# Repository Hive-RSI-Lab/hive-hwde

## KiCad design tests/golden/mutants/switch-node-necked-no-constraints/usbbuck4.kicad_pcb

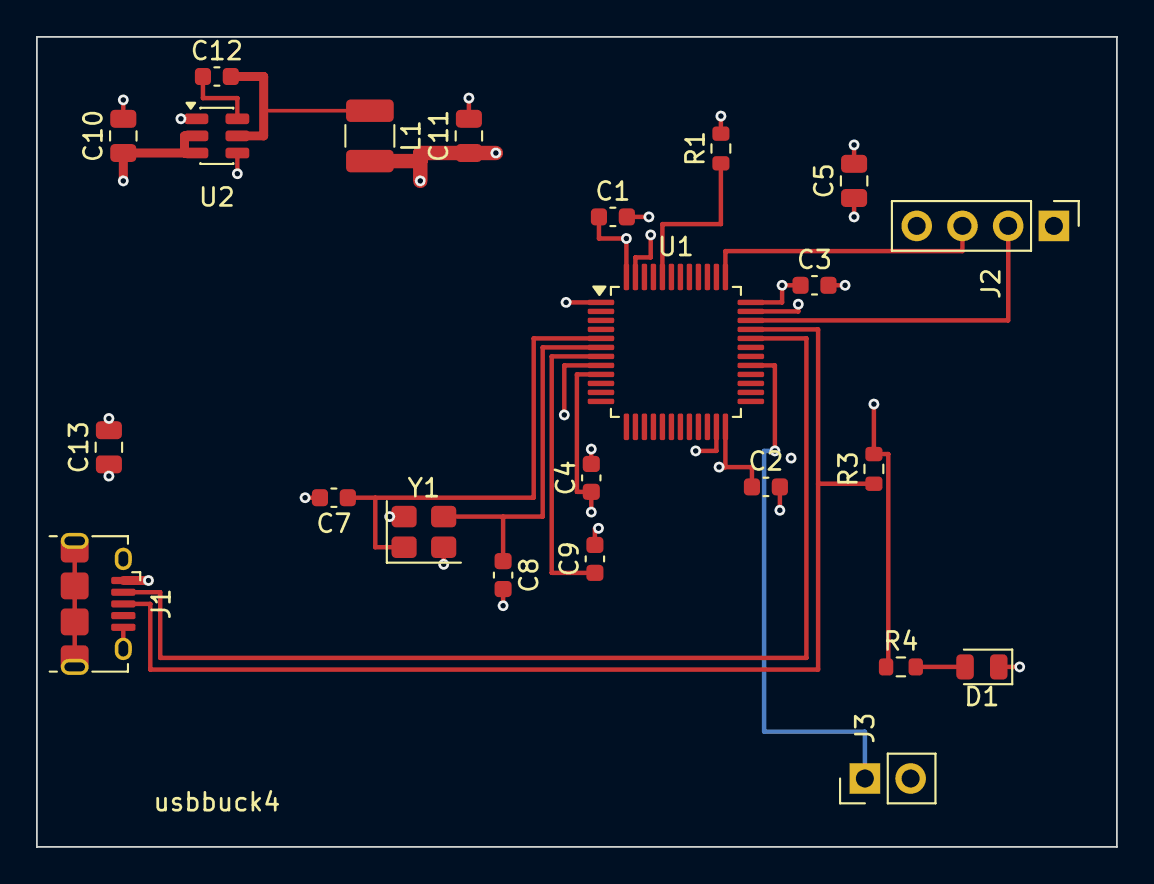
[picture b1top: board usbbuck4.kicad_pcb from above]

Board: 4 copper layers, 60.0 x 45.0 mm, 23 parts (0 on the bottom side), 15 nets.

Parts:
C1, C2, C3, C4, C9, C12: 100nF; C_0603_1608Metric
C5, C10: 10uF; C_0805_2012Metric
C7, C8: 22pF; C_0603_1608Metric
C11: 22uF; C_0805_2012Metric
C13: 4.7uF; C_0805_2012Metric
D1: LED_pwr; LED_0805_2012Metric
J1: USB_micro; USB_Micro-B_Amphenol_10118194_Horizontal
J2: SWD; PinHeader_1x04_P2.54mm_Vertical
J3: MCO_OUT; PinHeader_1x02_P2.54mm_Vertical
L1: 4.7uH; L_1210_3225Metric
R1: 10k; R_0603_1608Metric
R3: 1k5; R_0603_1608Metric
R4: 1k; R_0603_1608Metric
U1: STM32F103C8T6; LQFP-48_7x7mm_P0.5mm
U2: AP63203WU; TSOT-23-6
Y1: 8MHz; Crystal_SMD_3225-4Pin_3.2x2.5mm

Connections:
+3V3: C1.1, C2.1, C3.1, C4.1, C5.1, C11.1, J2.1, L1.2, R3.2, R4.1, U1.1, U1.9, U1.24, U1.36, U1.48, U2.1
/BOOT0: R1.1, U1.44
/BST: C12.1, U2.6
/LED_A: D1.2, R4.2
/MCO: J3.1, U1.29
/NRST: C9.1, U1.7
/OSC_IN: C7.1, U1.5, Y1.1
/OSC_OUT: C8.1, U1.6, Y1.3
/SW: C12.2, L1.1, U2.5 (SW)
/SWCLK: J2.3, U1.37
/SWDIO: J2.2, U1.34
/USB_DM: J1.2, U1.32
/USB_DP: J1.3, R3.1, U1.33
GND: C1.2, C2.2, C3.2, C4.2, C5.2, C7.2, C8.2, C9.2, C10.2, C11.2, C13.2, D1.1, J1.5, J1.SH, J2.4, J3.2, R1.2, U1.8, U1.23, U1.35, U1.47, U2.4, Y1.2, Y1.4
VBUS: C10.1, C13.1, J1.1, U2.2, U2.3

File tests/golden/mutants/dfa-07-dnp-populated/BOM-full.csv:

Comment,Designator,Qty Per Board,Footprint,MPN,LCSC,Assembly Class,Instructions
PWR_5V,J1,1,PinHeader_1x02_P2.54mm_Vertical,,,smt_placed,
SWD,J2,1,PinHeader_1x04_P2.54mm_Vertical,,,smt_placed,
22pF,"C8,C7",2,C_0603_1608Metric,,,smt_placed,
10uF,"C5,C6",2,C_0805_2012Metric,,,smt_placed,
8MHz,Y1,1,Crystal_SMD_3225-4Pin_3.2x2.5mm,,,smt_placed,
100nF,"C9,C1,C2,C3,C4",5,C_0603_1608Metric,,,smt_placed,
10k,R1,1,R_0603_1608Metric,,,smt_placed,
STM32F103C8T6,U1,1,LQFP-48_7x7mm_P0.5mm,,,smt_placed,
AMS1117-3.3,U2,1,SOT-223-3_TabPin2,,,smt_placed,
470,R2,1,R_0603_1608Metric,,,smt_placed,
LED_red,D1,1,LED_0805_2012Metric,,,smt_placed,
